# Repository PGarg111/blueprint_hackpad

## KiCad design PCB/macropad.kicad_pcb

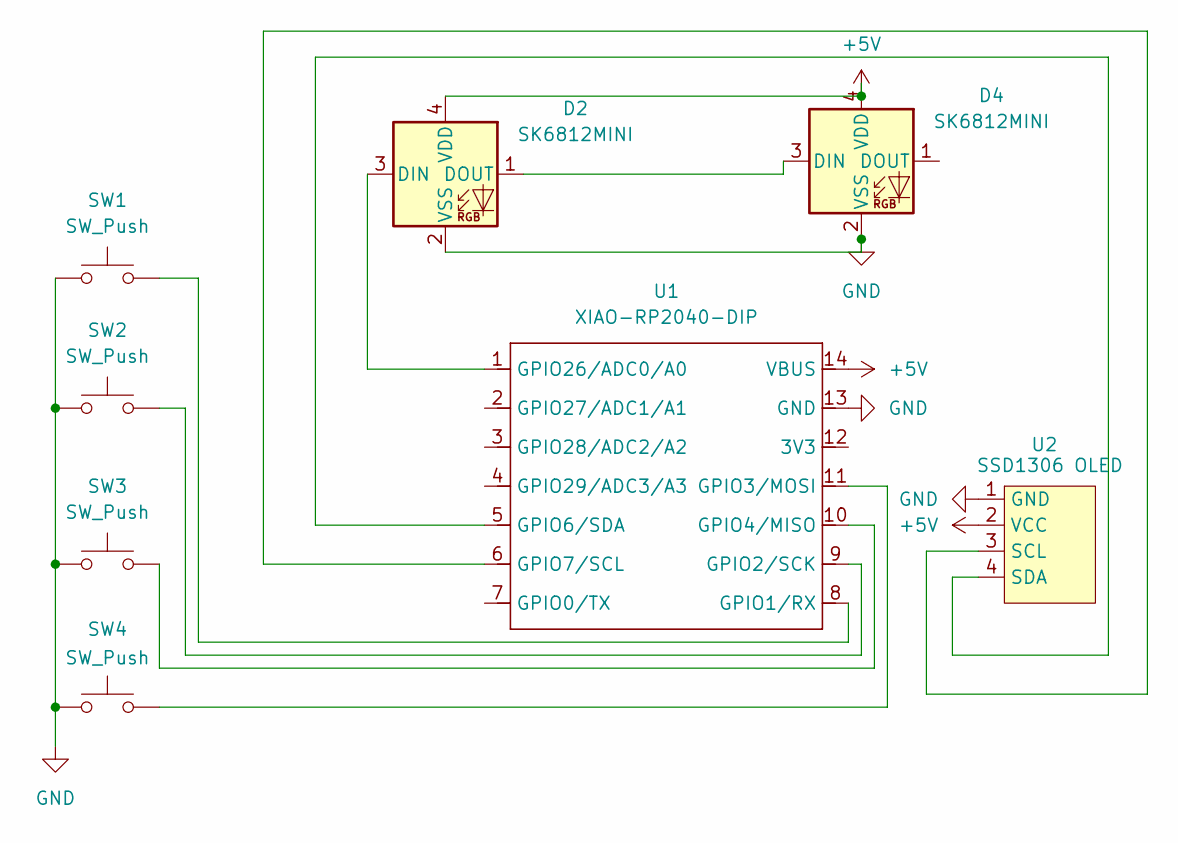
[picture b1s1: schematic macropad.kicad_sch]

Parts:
D2, D4: SK6812MINI; LED_SK6812MINI_PLCC4_3.5x3.5mm_P1.75mm
SW1, SW2, SW3, SW4: SW_Push; SW_Cherry_MX_1.00u_PCB
U1: XIAO-RP2040-DIP
U2: SSD1306 OLED; PinHeader_1x04_P2.54mm_Vertical

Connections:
+5V: D2.4 (VDD), D4.4 (VDD), U1.14 (VBUS), U2.2 (VCC)
GND: D2.2 (VSS), D4.2 (VSS), SW1.1, SW2.1, SW3.1, SW4.1, U1.13 (GND), U2.1 (GND)
unnamed: D2.3 (DIN), U1.1 (GPIO26/ADC0/A0)
unnamed: D2.1 (DOUT), D4.3 (DIN)
unnamed: SW1.2, U1.8 (GPIO1/RX)
unnamed: SW2.2, U1.9 (GPIO2/SCK)
unnamed: SW4.2, U1.11 (GPIO3/MOSI)
unnamed: SW3.2, U1.10 (GPIO4/MISO)
unnamed: U1.5 (GPIO6/SDA), U2.4 (SDA)
unnamed: U1.6 (GPIO7/SCL), U2.3 (SCL)

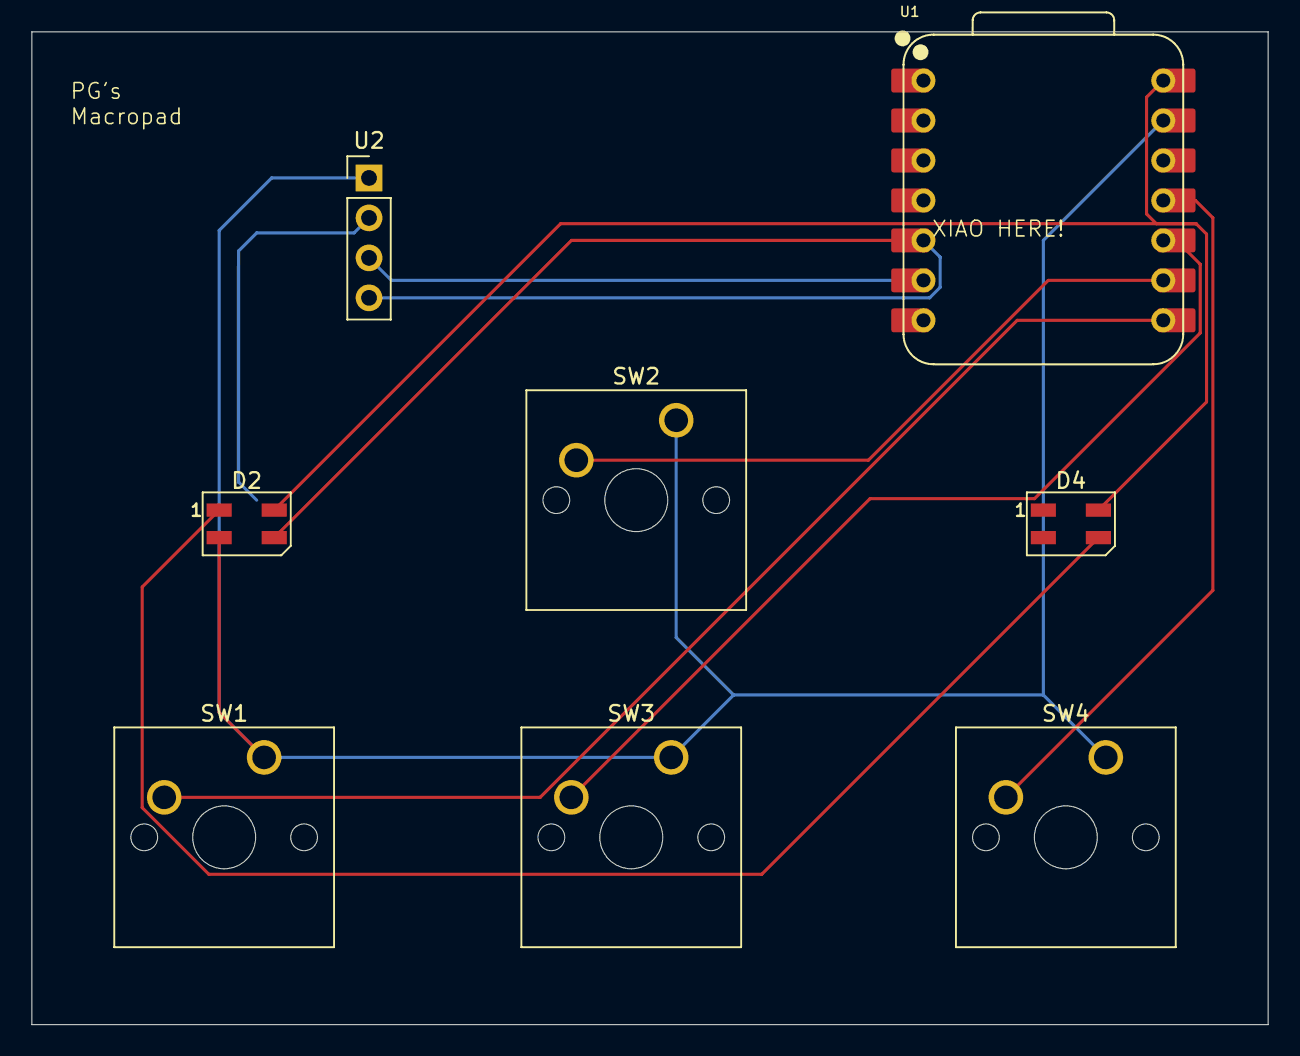
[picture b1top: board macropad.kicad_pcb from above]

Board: 2 copper layers, 78.6 x 63.1 mm, 8 parts (0 on the bottom side), 10 nets.

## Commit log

2025-12-30 Fix typo in project name from 'bluepring' to 'blueprint'
2025-12-30 added code with python and all needed files
2025-12-30 put in edited fusion 360 file
